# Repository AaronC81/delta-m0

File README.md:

# Delta M0

## What is this?

Delta M0 is a **basic, compact scientific calculator** based on an STM32F0
microcontroller.

In use | Front | Back
:-:|:-:|:-:
 |  | 

## How well does it work?

It does _work_, but you probably don't want to use it as an actual calculator
yet. The software is really lacking.

## Project structure

This is based off the
[libopencm3 template](https://github.com/libopencm3/libopencm3-template).

  - `my-project` contains the C code for the firmware.
  - `test` is a small set of unit tests which you can run with `./test/run`.
  - `hardware` contains the KiCad files for the PCB. 

# Building

Make sure you clone with `--recurse-submodules`!

Then:

```
make -C libopencm3
make -C my-project
```

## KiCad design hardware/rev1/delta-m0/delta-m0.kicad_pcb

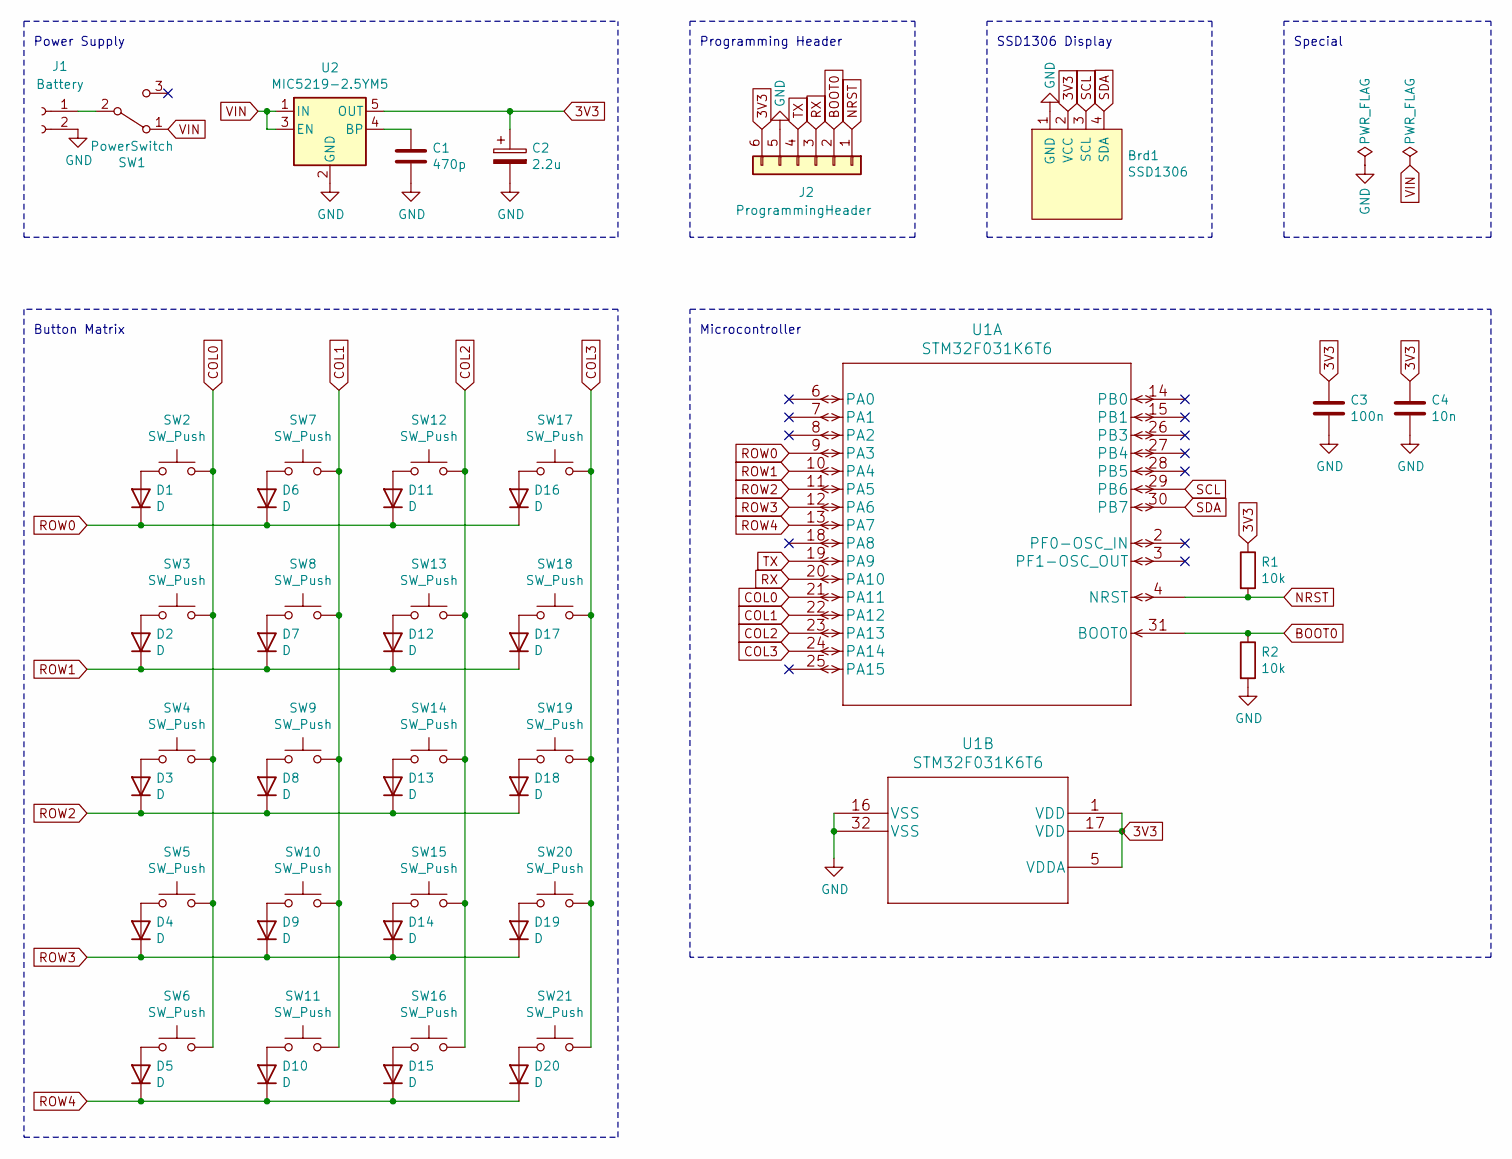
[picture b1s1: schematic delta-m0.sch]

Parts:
Brd1: SSD1306; 128x64OLED
C1: 470p; C_0805_2012Metric_Pad1.18x1.45mm_HandSolder
C2: 2.2u; C_0805_2012Metric_Pad1.18x1.45mm_HandSolder
C3: 100n; C_0805_2012Metric_Pad1.18x1.45mm_HandSolder
C4: 10n; C_0805_2012Metric_Pad1.18x1.45mm_HandSolder
D1, D2, D3, D4, D5, D6, D7, D8, D9, D10, D11, D12, D13, D14, D15, D16, D17, D18, D19, D20: D; D_SOD-123
J1: Battery; JST_PH_S2B-PH-K_1x02_P2.00mm_Horizontal
J2: ProgrammingHeader; PinSocket_1x06_P2.54mm_Vertical
R1, R2: 10k; R_0603_1608Metric_Pad0.98x0.95mm_HandSolder
SW1: PowerSwitch; SW_SPDT_CK-JS102011SAQN
SW2, SW3, SW4, SW5, SW6, SW7, SW8, SW9, SW10, SW11, SW12, SW13, SW14, SW15, SW16, SW17, SW18, SW19, SW20, SW21: SW_Push; PTS636
U1: STM32F031K6T6; TQFP-32_7x7mm_P0.8mm
U2: MIC5219-2.5YM5; SOT-23-5

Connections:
3V3: Brd1.2 (VCC), C2.1, C3.1, C4.1, J2.6, R1.1, U1.1 (VDD), U1.5 (VDDA), U1.17 (VDD), U2.5 (OUT)
BOOT0: J2.2, R2.1, U1.31 (BOOT0)
COL0: SW2.2, SW3.2, SW4.2, SW5.2, SW6.2, U1.21 (PA11)
COL1: SW7.2, SW8.2, SW9.2, SW10.2, SW11.2, U1.22 (PA12)
COL2: SW12.2, SW13.2, SW14.2, SW15.2, SW16.2, U1.23 (PA13)
COL3: SW17.2, SW18.2, SW19.2, SW20.2, SW21.2, U1.24 (PA14)
GND: Brd1.1 (GND), C1.2, C2.2, C3.2, C4.2, J1.2, J2.5, R2.2, U1.16 (VSS), U1.32 (VSS), U2.2 (GND)
NRST: J2.1, R1.2, U1.4 (NRST)
unnamed: C1.1, U2.4 (BP)
unnamed: D1.2 (A), SW2.1
unnamed: D2.2 (A), SW3.1
unnamed: D3.2 (A), SW4.1
unnamed: D4.2 (A), SW5.1
unnamed: D5.2 (A), SW6.1
unnamed: D6.2 (A), SW7.1
unnamed: D7.2 (A), SW8.1
unnamed: D8.2 (A), SW9.1
unnamed: D9.2 (A), SW10.1
unnamed: D10.2 (A), SW11.1
unnamed: D11.2 (A), SW12.1
unnamed: D12.2 (A), SW13.1
unnamed: D13.2 (A), SW14.1
unnamed: D14.2 (A), SW15.1
unnamed: D15.2 (A), SW16.1
unnamed: D16.2 (A), SW17.1
unnamed: D17.2 (A), SW18.1
unnamed: D18.2 (A), SW19.1
unnamed: D19.2 (A), SW20.1
unnamed: D20.2 (A), SW21.1
unnamed: J1.1, SW1.2 (B)
ROW0: D1.1 (K), D6.1 (K), D11.1 (K), D16.1 (K), U1.9 (PA3)
ROW1: D2.1 (K), D7.1 (K), D12.1 (K), D17.1 (K), U1.10 (PA4)
ROW2: D3.1 (K), D8.1 (K), D13.1 (K), D18.1 (K), U1.11 (PA5)
ROW3: D4.1 (K), D9.1 (K), D14.1 (K), D19.1 (K), U1.12 (PA6)
ROW4: D5.1 (K), D10.1 (K), D15.1 (K), D20.1 (K), U1.13 (PA7)
RX: J2.3, U1.20 (PA10)
SCL: Brd1.3 (SCL), U1.29 (PB6)
SDA: Brd1.4 (SDA), U1.30 (PB7)
TX: J2.4, U1.19 (PA9)
VIN: SW1.1 (A), U2.1 (IN), U2.3 (EN)

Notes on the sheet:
Power Supply
Programming Header
SSD1306 Display
Microcontroller
Button Matrix
Special

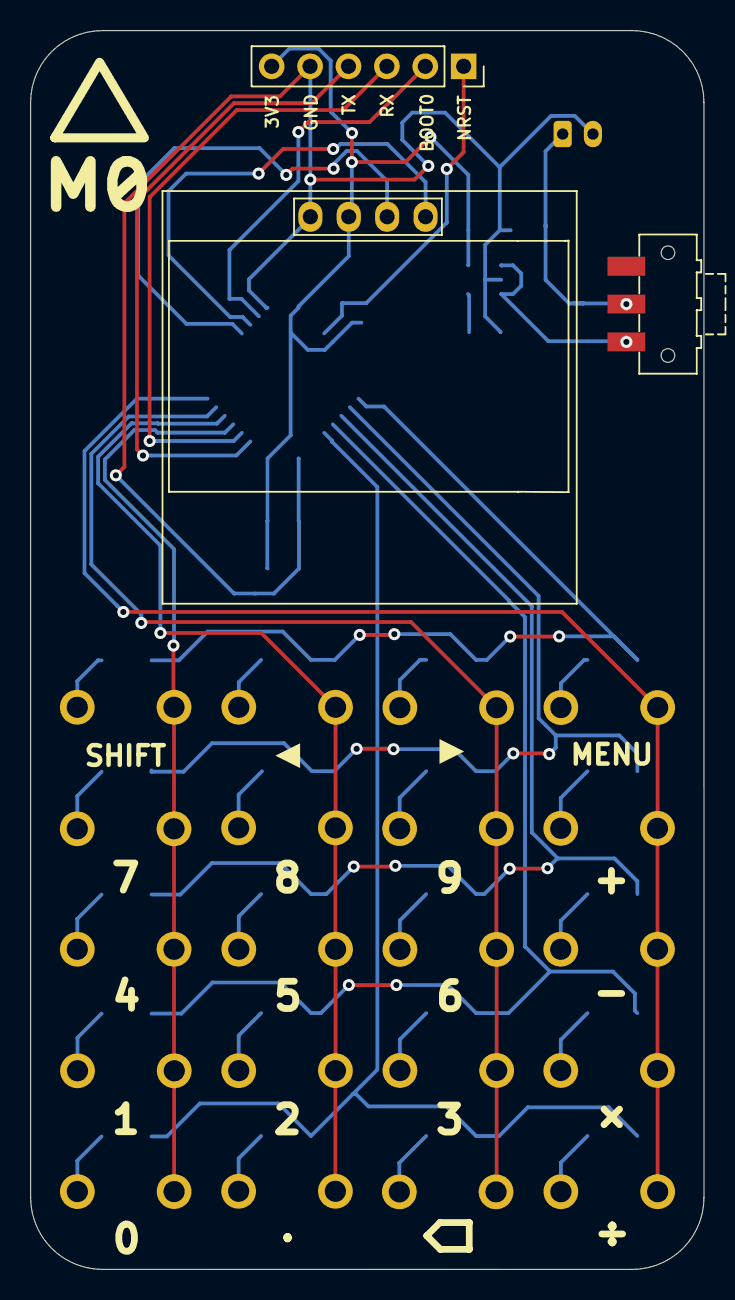
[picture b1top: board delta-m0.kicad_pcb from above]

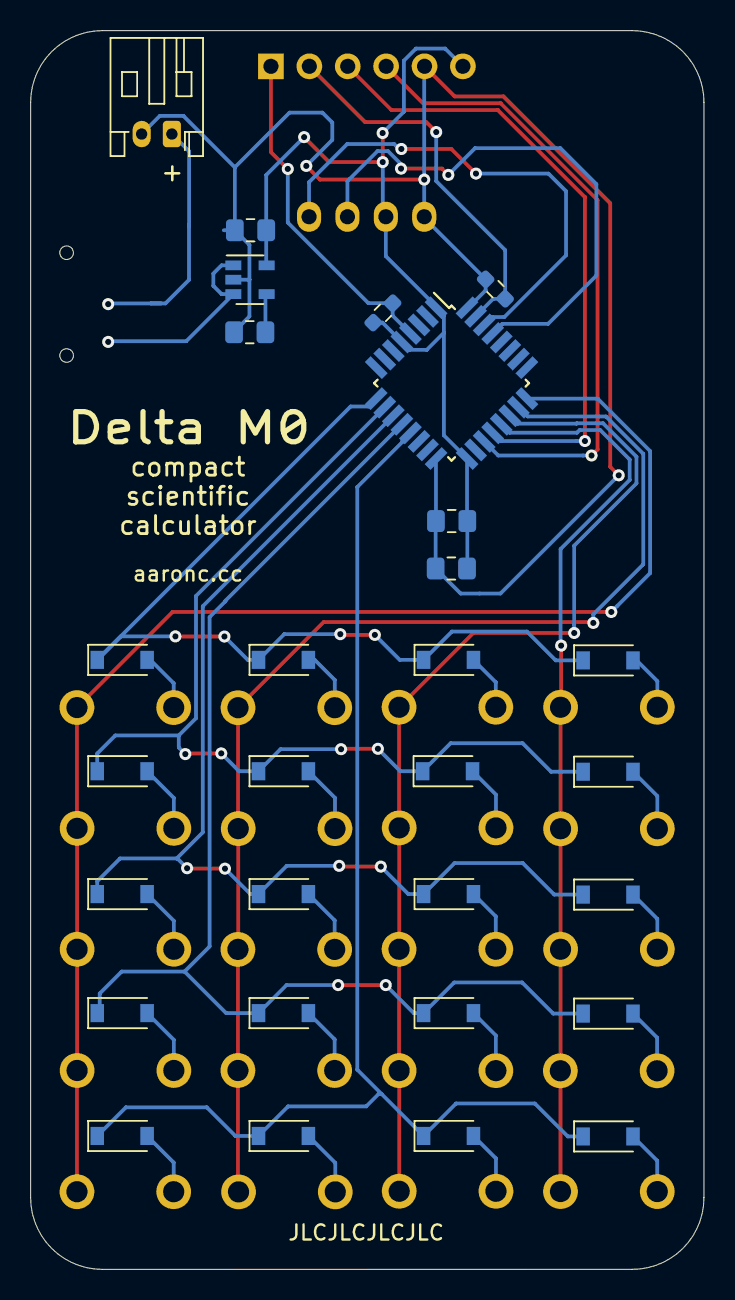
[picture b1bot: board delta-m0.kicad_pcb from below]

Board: 2 copper layers, 44.5 x 82.0 mm, 52 parts (29 on the bottom side), 40 nets.

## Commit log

2020-11-24 Add graphics
2020-11-25 Add keypad, tokens and input
2020-11-25 Add proper key-mapping input and some more tokens
2020-11-25 Show a (bad) cursor and let us move it
2020-11-25 Fix insertion trashing everything afterwards
2020-11-25 Fix insertion... again
2020-11-29 Move token_index_t
2020-11-29 Add basic evaluator
2020-11-29 Add basic tests for evaluator
2020-11-29 Add expression evaluation
2020-11-30 Add the rest of the digits
2020-11-30 Draw calculation results, fix display not working on power-on
2020-12-02 Added hardware
2020-12-21 Update Kicad PCB
2020-12-21 Change MCU
2020-12-21 Update .gitignore for gerbers
2020-12-21 Expand README
2020-12-21 Make images 10x smaller
2020-12-21 Show the images more nicely
2020-12-23 Move multiply key to where it is on hardware
2020-12-23 Add a basic font, with a converter
2020-12-23 Add a text library
2020-12-24 Rename "dot" to "multiply", add subtract and divide
2020-12-24 Add dodgy subtract/divide implementation, and display of negative numbers
2021-01-07 Add a function for testing expressions
2021-01-07 Add fancy macro for producing token arrays
2021-01-12 Add the beginnings of a shunting yard based parser
2021-01-12 Let VSCode debug tests
2021-01-12 Implement postfix evaluation
2021-01-12 Use new shunt evaluator for calculations
2021-01-12 Make evaluator_evaluate errors not cause result to be "bonus number"
2021-01-12 Make deletion work
2021-01-12 Add shift
2021-01-12 Add shift+del=clear, fix delete, fix insert at idx 0
2021-01-13 Make input not flicker the whole screen, only the bit which changed
2021-01-13 Fix answer smearing
2021-01-13 Blank on clear
2021-01-13 Treat an empty expression as 0
2021-01-14 Print 0 if the answer is 0, rather than nothing
2021-01-17 Fix undefined return when evaluating empty
2021-01-17 Add unary operators
2021-01-17 Fix basic unary negative evaluation
2021-01-17 Fix unary minus at end of expressions
